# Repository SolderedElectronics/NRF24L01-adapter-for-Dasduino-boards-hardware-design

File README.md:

# NRF24L01 adapter for Dasduino boards Hardware Design

## About the Product

|  |
| :----------------------------------------------------------: |
| [Buy NRF24L01 adapter for Dasduino boards](https://www.solde.red/333059) |

Connecting the NRF24L01 can be tricky – you have to pay attention to the layout of the pins, adjust them to match those from the library and add a capacitor. This board solves all that, and it already comes with soldered headers, so just plug this board into your Dasduino and that’s it!

---

## Repository Contents

This repository contains all design files for NRF24L01 adapter for Dasduino boards, organized as follows:

- **`CAD` folder**: Contains KiCAD design files, including:
  - Schematics
  - PCB layout
  - Panel PCB layout
  - Source 3D files in Fusion360, if any
  - All files are sorted by version with a detailed change log.
- **`OUTPUTS` folder**: Includes all production-ready files, such as:
  - Bill of Materials (BOM) and interactive BOM (iBOM)
  - PDF versions of schematics
  - 3D `.step` file of the board
  - 3D-printable models
  - Gerber files for PCB manufacturing
  - Image of the pinout of the board
  - Product image
  - Compliance, legal and generic sales documents

Refer to the `Change Log` in the CAD folder for details about updates between versions.

---

## Learn More About the Product

Beyond the repository, explore the following resources:

### Soldered Verify

The **Soldered Verify** system ensures every board you purchase from Soldered is fully functional. It also provides access to exclusive test data for your product. To get started, find the unique Soldered Verify ID on your product's packaging and enter the ID on the [Soldered Verify page](https://soldered.com/verify/) to access test results and additional product details.

### Soldered Community

Soldered Community is your go-to place for technical support. Our engineers track and answer all questions posted there, and it’s a great space for the maker community. Get answers to your questions and solutions for your challenges at [Soldered Community](https://soldered.com/community).

### solde.red

solde.red is an ultimate URL shortener and information hub. Access it by typing solde.red/ followed by your product SKU, e.g., [solde.red/333000](https://solde.red/333000), to find getting-started guides, datasheets, open-source hardware and software files, certifications, images, pinouts, and more. Read more about the shortener [here](https://solde.red/info/).

---

## Contributing

Contributions are welcome! Here’s how you can get involved:

- Submit pull requests to enhance the design or fix issues.
- Report bugs or problems by opening an issue.

We encourage community collaboration to make this product even better.

---

## About Soldered

[Soldered for Makers](https://soldered.com) specializes in designing and manufacturing electronic products tailored for enthusiasts, ranging from hobbyists to professionals. Our portfolio includes electronic boards, sensors, and actuators that are widely utilized in fields such as microelectronics, mechatronics, robotics, programming, and IoT. Every product we offer is designed in-house and built upon open-source hardware and software platforms. Proudly certified and manufactured within the European Union, our catalog likely includes the product you need for your project.

We complement these products with comprehensive tutorials and manuals, product descriptions, schematics, programming codes, and project examples. Our round-the-clock [customer and technical support](https://soldered.com/community) is available for all our products, irrespective of the sales channel. Soldered’s success and services reflect our maker community’s unwavering [trust](https://www.trustpilot.com/review/soldered.com), for which we are deeply grateful. Join our community and create using Soldered products.

---

## License

All Soldered open-source hardware (OSH) is under The TAPR Open Hardware License. Read more in the LICENSE file located in this repository.

**Disclaimer:**

No warranty - all designs in this repository are distributed in the hope that they will be useful, but without any warranty. They are provided "AS IS", therefore without warranty of any kind, either expressed or implied. The entire quality and performance of what you do with the contents of this repository are your responsibility. In no event Soldered Electronics will be liable for your damages, or losses, including any general, special, incidental, or consequential damage arising out of the use or inability to use the contents of this repository. 

---

## Have fun!

Thank you for your support from your fellow makers at Soldered Electronics.

Happy Making!

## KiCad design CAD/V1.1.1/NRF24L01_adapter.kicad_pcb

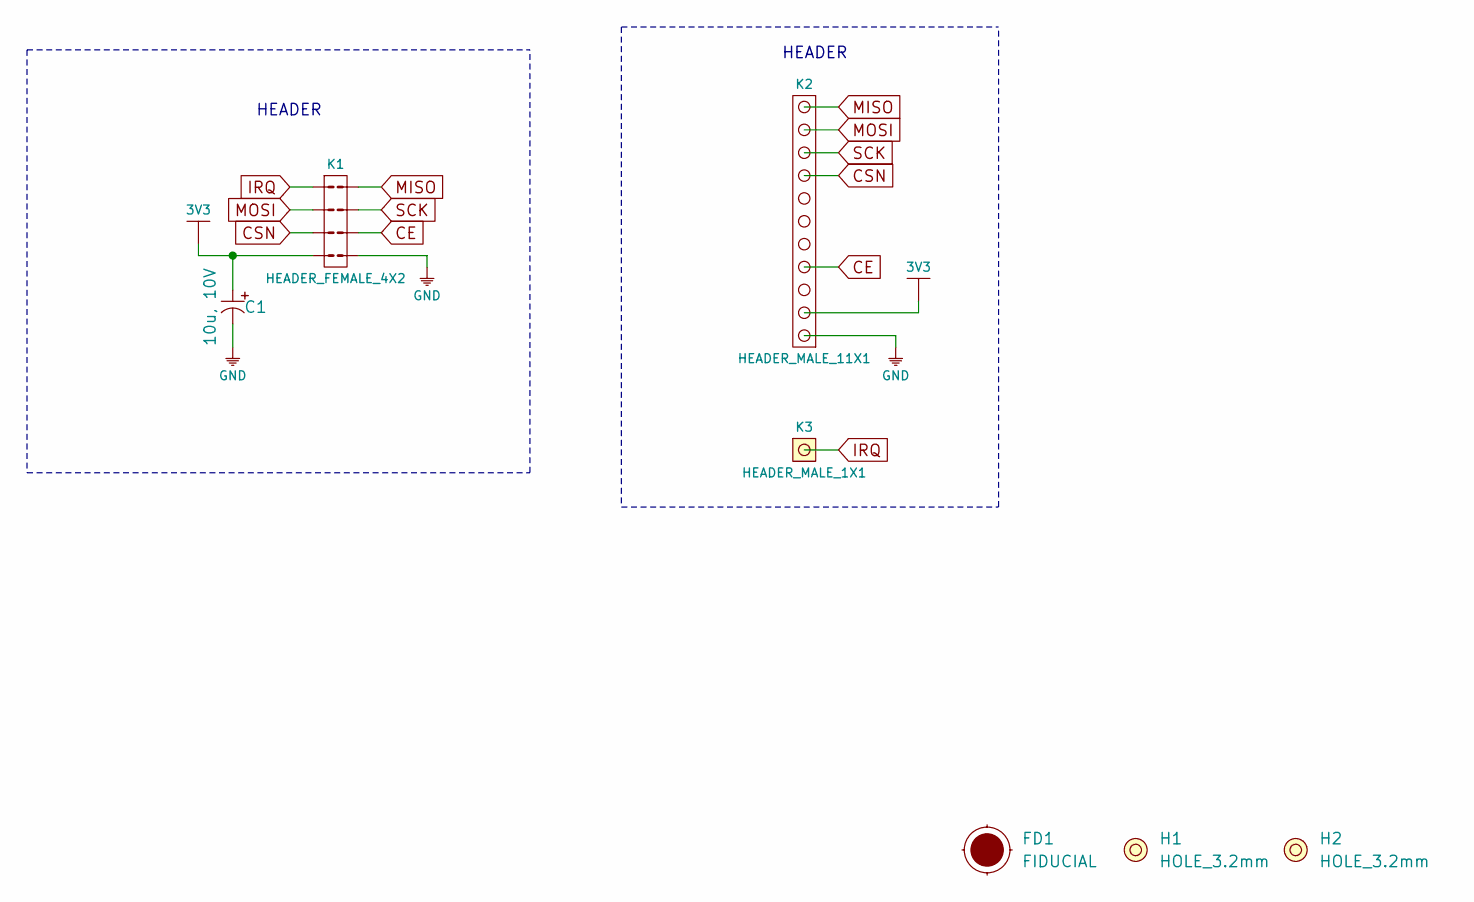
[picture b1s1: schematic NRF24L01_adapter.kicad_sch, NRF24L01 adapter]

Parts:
C1: 10u, 10V; ELECTROLITIC_CAP_4mm
FD1: FIDUCIAL; FIDUCIAL_23
H1, H2: HOLE_3.2mm
K1: HEADER_FEMALE_4X2
K2: HEADER_MALE_11X1
K3: HEADER_MALE_1X1

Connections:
3V3: C1.1 (+), K1.4, K2.2
CE: K1.6, K2.4
CSN: K1.3, K2.8
GND: C1.2 (-), K1.5, K2.1
IRQ: K1.1, K3.1
MISO: K1.8, K2.11
MOSI: K1.2, K2.10
SCK: K1.7, K2.9

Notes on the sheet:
HEADER
HEADER

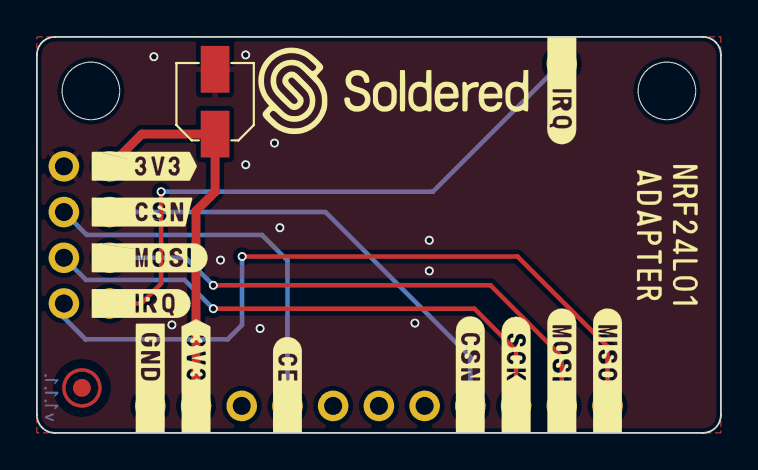
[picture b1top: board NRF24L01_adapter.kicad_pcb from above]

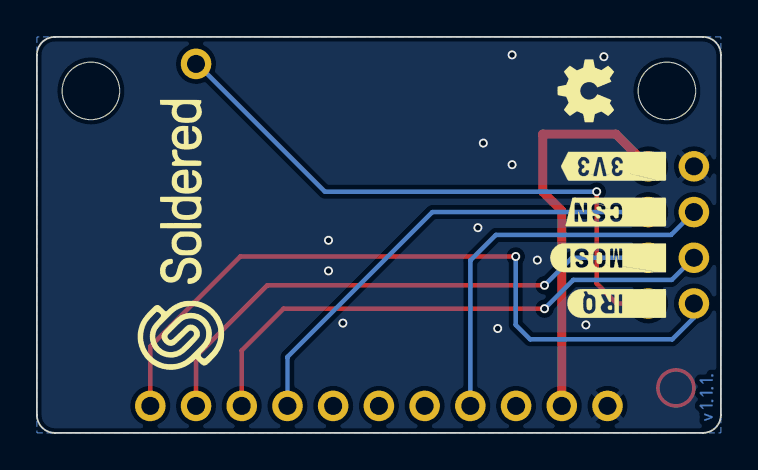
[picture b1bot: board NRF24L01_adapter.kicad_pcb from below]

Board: 2 copper layers, 38.0 x 22.0 mm, 7 parts (2 on the bottom side), 8 nets.

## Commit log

2022-08-06 Updating open source files.
